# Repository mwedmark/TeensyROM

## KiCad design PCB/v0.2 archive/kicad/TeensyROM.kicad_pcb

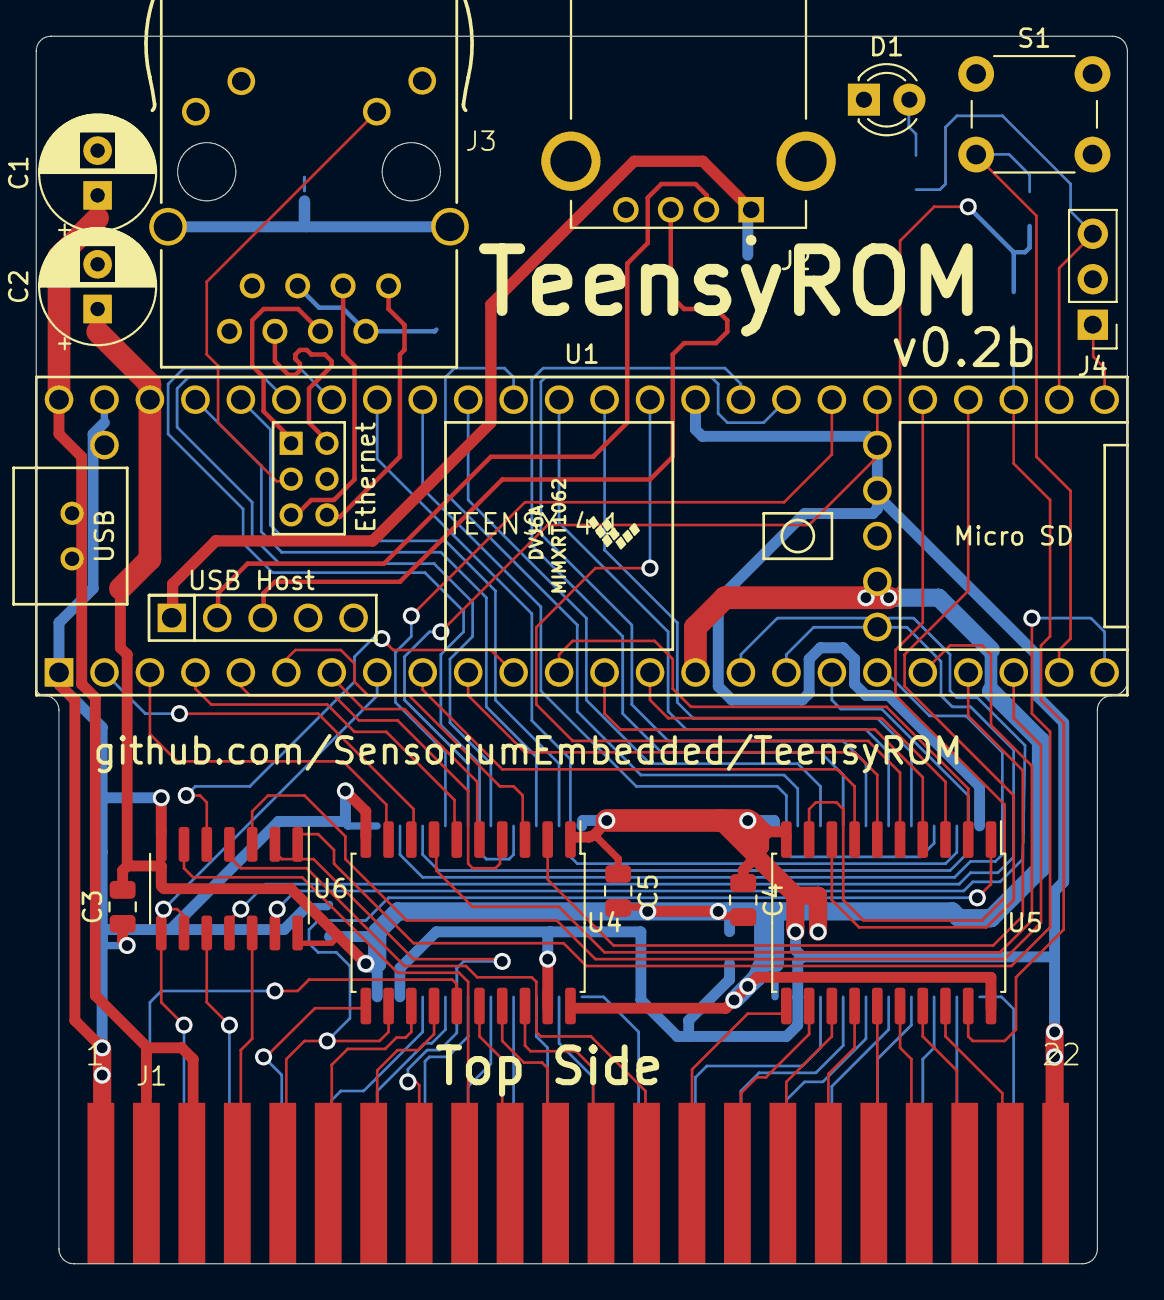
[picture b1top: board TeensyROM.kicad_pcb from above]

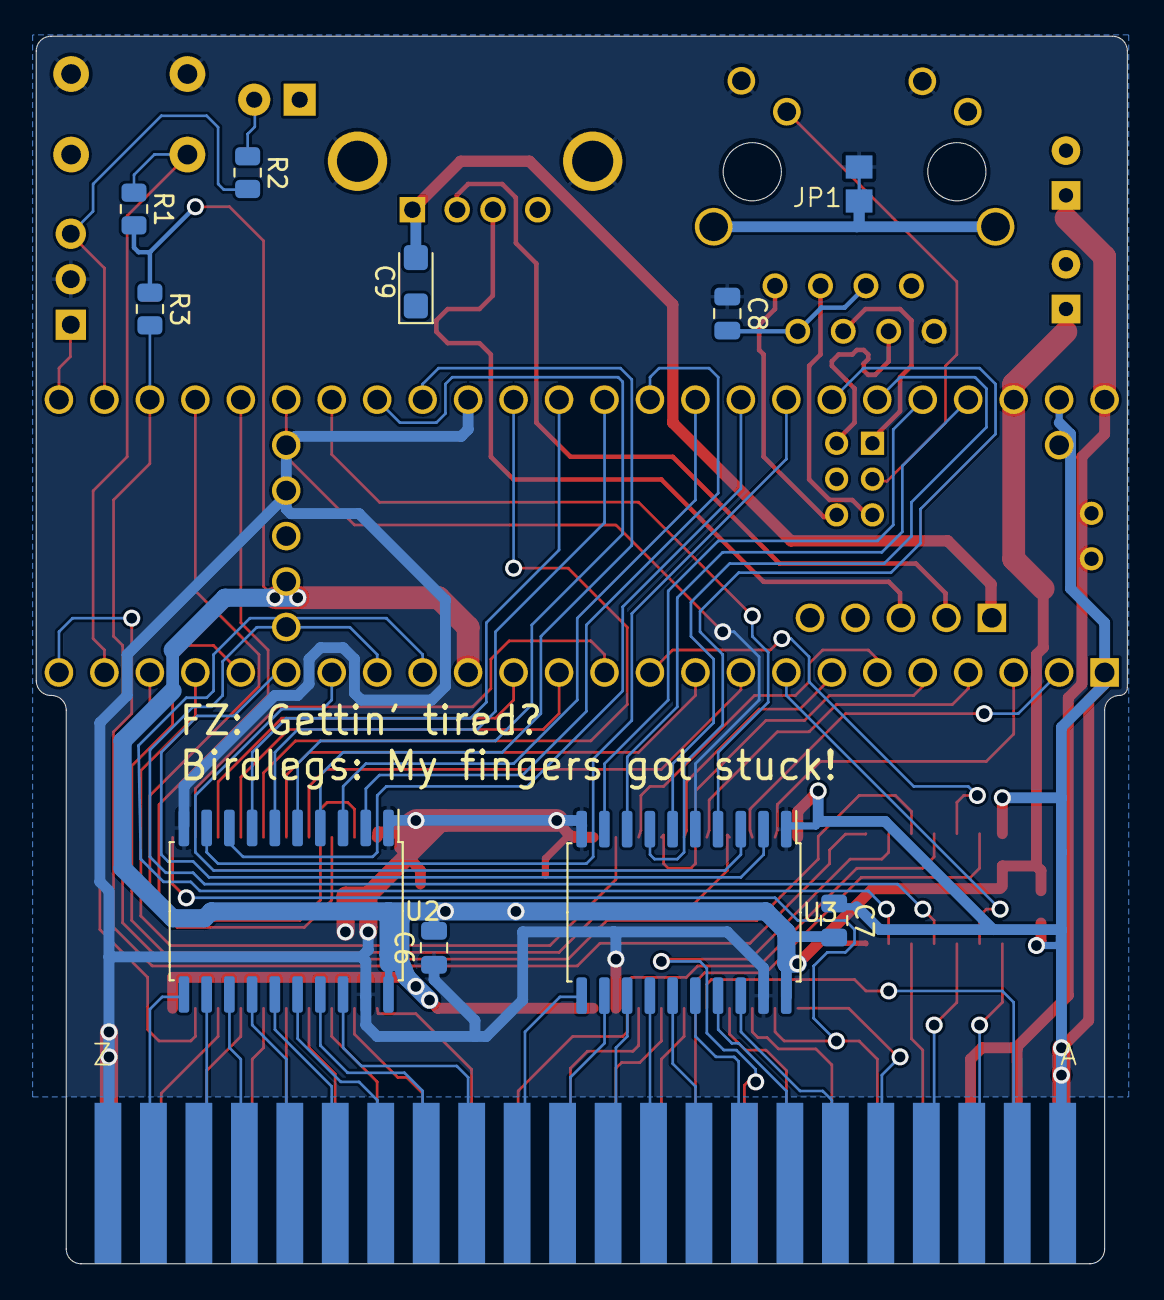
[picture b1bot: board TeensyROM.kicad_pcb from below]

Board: 2 copper layers, 61.0 x 68.6 mm, 25 parts (10 on the bottom side), 7 nets.

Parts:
C1, C2: 100uF; CP_Radial_D6.3mm_P2.50mm
C3, C4, C5, C6, C7, C8: 0.1 uF; C_0805_2012Metric
C9: 100uF; CP_EIA-3216-18_Kemet-A
D1: GRN; LED_D3.0mm
J1: C64-EXPANSION-PORT; EXPANSIO_SQ
J2: 292303-1; TE_292303-1
J3: J1B1211CCD; CONN12_J1B1211CCD_WIZ
J4: 3 pin Header; PinHeader_1x03_P2.54mm_Vertical
JP1: SHORTSMT; SHORT
R1, R3: 10k; R_0805_2012Metric
R2: 1k; R_0805_2012Metric
S1: SW-MOM; SW_PUSH_6mm_H5mm
U1: TEENSY41; Teensy41
U2, U3, U4, U5: 74LCV245; SOIC-20W_7.5x12.8mm_P1.27mm
U6: 74LVC07; SOIC-14_3.9x8.7mm_P1.27mm

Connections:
+3V3: C3.2, C4.2, C5.2, C6.2, C7.2, R1.2, R3.1, U2.20 (VCC), U3.20 (VCC), U4.20 (VCC), U5.20 (VCC), U6.14 (VCC)
/LED: J4.3, R2.2
/R/~W: U4.12 (B7), U5.1 (DIR)
/~DATA_CE: R3.2, U5.19 (G)
GND: C3.1, C4.1, C5.1, C6.1, C7.1, C8.1, J2.SH1 (5), J2.SH2 (6), J3.8 (C_GND), J3.9 (C), J3.11 (C1), J4.2, JP1.1, S1.1, U2.1 (DIR), U2.10 (GND), U2.19 (G), U3.1 (DIR), U3.10 (GND), U3.19 (G), U4.1 (DIR), U4.10 (GND), U4.19 (G), U5.10 (GND), U6.7 (GND)
unnamed: C8.2, J3.2 (TCT), J3.5 (RCT)
unnamed: J3.S1, J3.S2, JP1.2

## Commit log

2023-12-08 Added v0.2 arch. version converted to Kicad
